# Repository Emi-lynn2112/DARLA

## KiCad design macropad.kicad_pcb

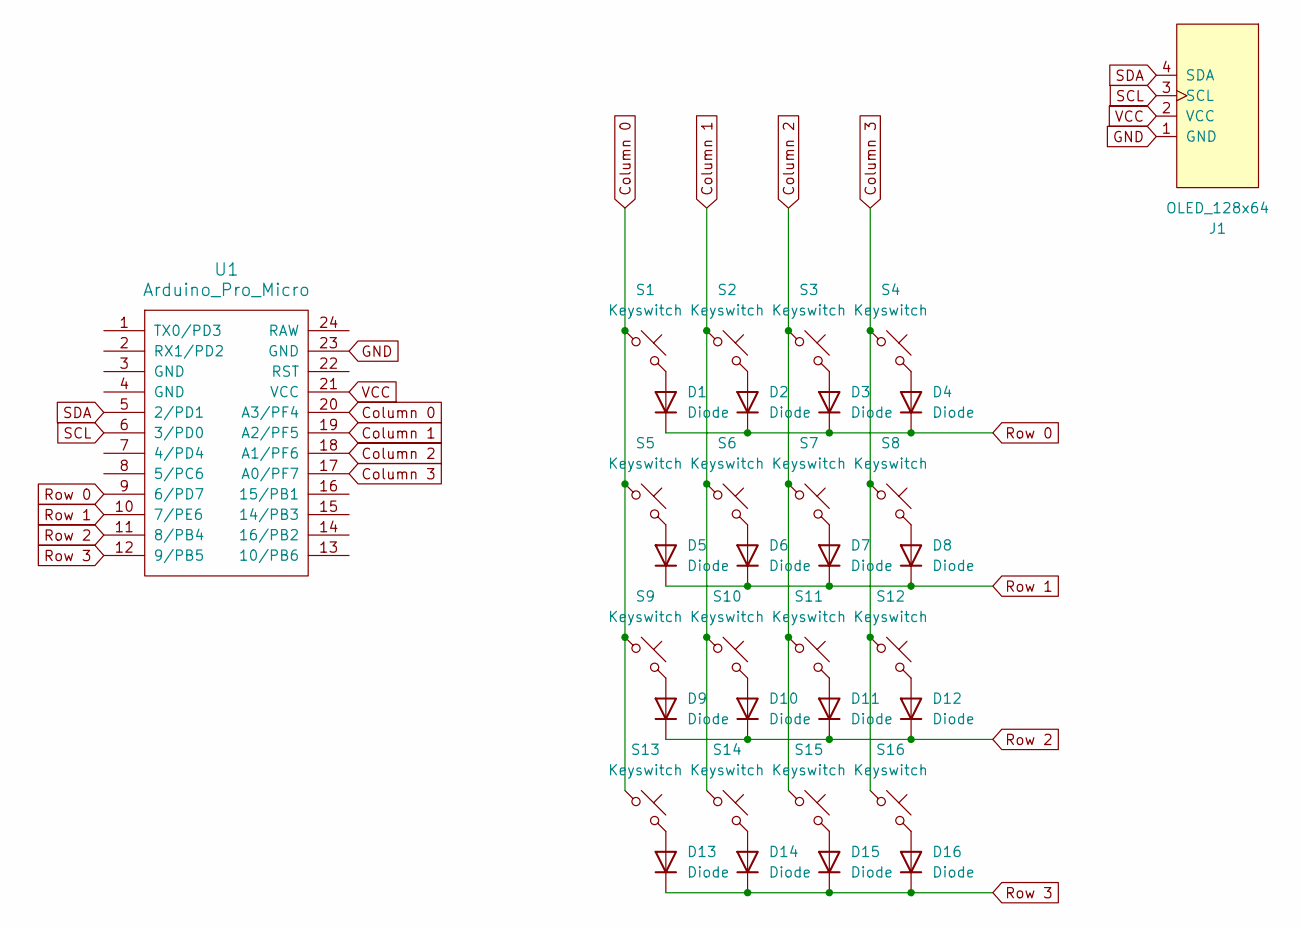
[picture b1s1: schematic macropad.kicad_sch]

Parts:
D1, D2, D3, D4, D5, D6, D7, D8, D9, D10, D11, D12, D13, D14, D15, D16: Diode; Diode_SOD-123
J1: OLED_128x64
S1, S2, S3, S4, S5, S6, S7, S8, S9, S10, S11, S12, S13, S14, S15, S16: Keyswitch; MX_PCB_1.00u
U1: Arduino_Pro_Micro

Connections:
Column 0: S1.1, S5.1, S9.1, S13.1, U1.20 (A3/PF4)
Column 1: S2.1, S6.1, S10.1, S14.1, U1.19 (A2/PF5)
Column 2: S3.1, S7.1, S11.1, S15.1, U1.18 (A1/PF6)
Column 3: S4.1, S8.1, S12.1, S16.1, U1.17 (A0/PF7)
GND: J1.1 (GND), U1.23 (GND)
unnamed: D1.2 (A), S1.2
unnamed: D2.2 (A), S2.2
unnamed: D3.2 (A), S3.2
unnamed: D4.2 (A), S4.2
unnamed: D5.2 (A), S5.2
unnamed: D6.2 (A), S6.2
unnamed: D7.2 (A), S7.2
unnamed: D8.2 (A), S8.2
unnamed: D9.2 (A), S9.2
unnamed: D10.2 (A), S10.2
unnamed: D11.2 (A), S11.2
unnamed: D12.2 (A), S12.2
unnamed: D13.2 (A), S13.2
unnamed: D14.2 (A), S14.2
unnamed: D15.2 (A), S15.2
unnamed: D16.2 (A), S16.2
Row 0: D1.1 (K), D2.1 (K), D3.1 (K), D4.1 (K), U1.9 (6/PD7)
Row 1: D5.1 (K), D6.1 (K), D7.1 (K), D8.1 (K), U1.10 (7/PE6)
Row 2: D9.1 (K), D10.1 (K), D11.1 (K), D12.1 (K), U1.11 (8/PB4)
Row 3: D13.1 (K), D14.1 (K), D15.1 (K), D16.1 (K), U1.12 (9/PB5)
SCL: J1.3 (SCL), U1.6 (3/PD0)
SDA: J1.4 (SDA), U1.5 (2/PD1)
VCC: J1.2 (VCC), U1.21 (VCC)

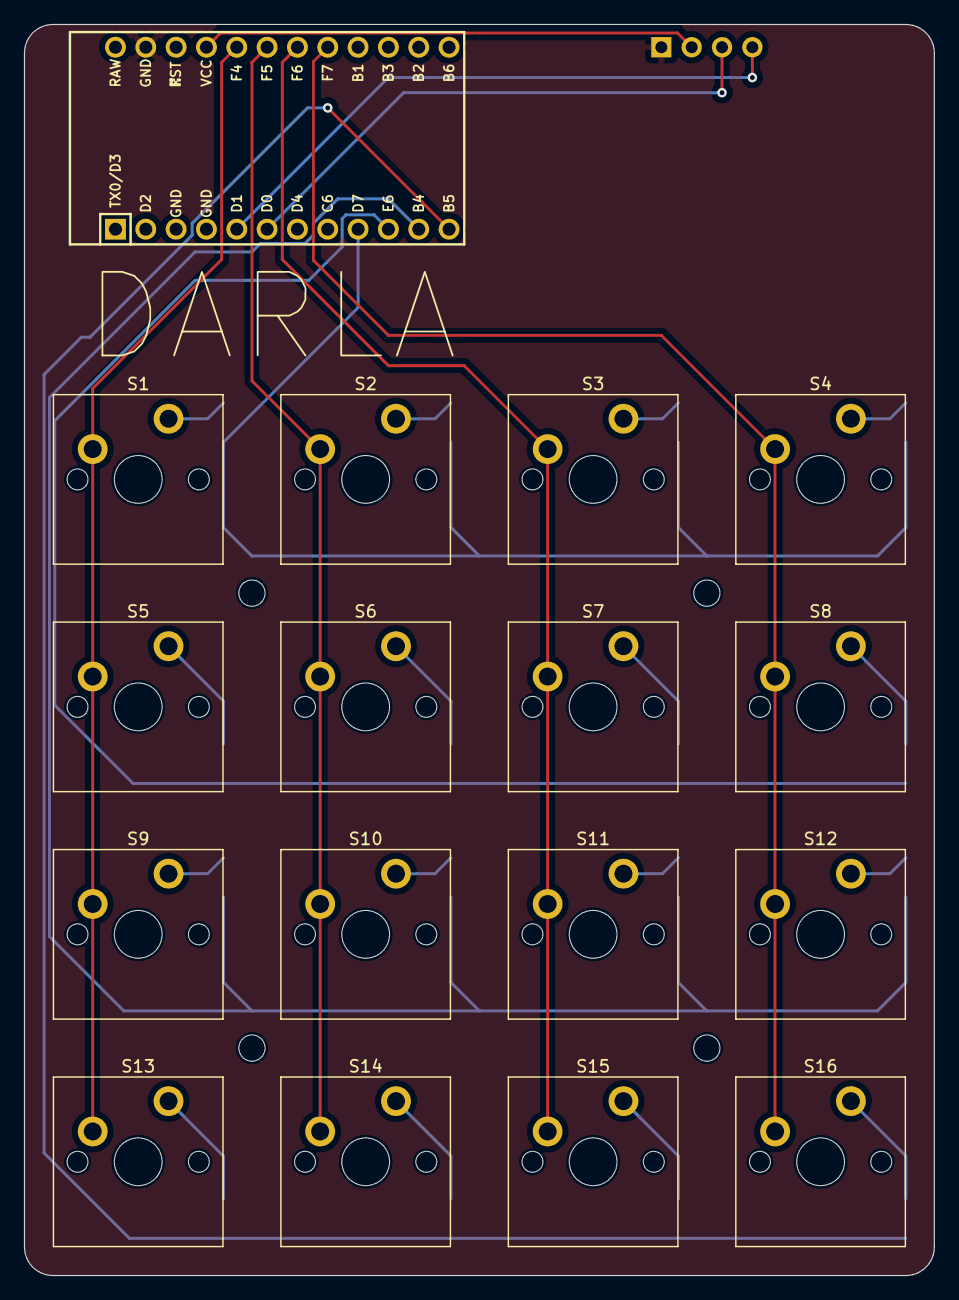
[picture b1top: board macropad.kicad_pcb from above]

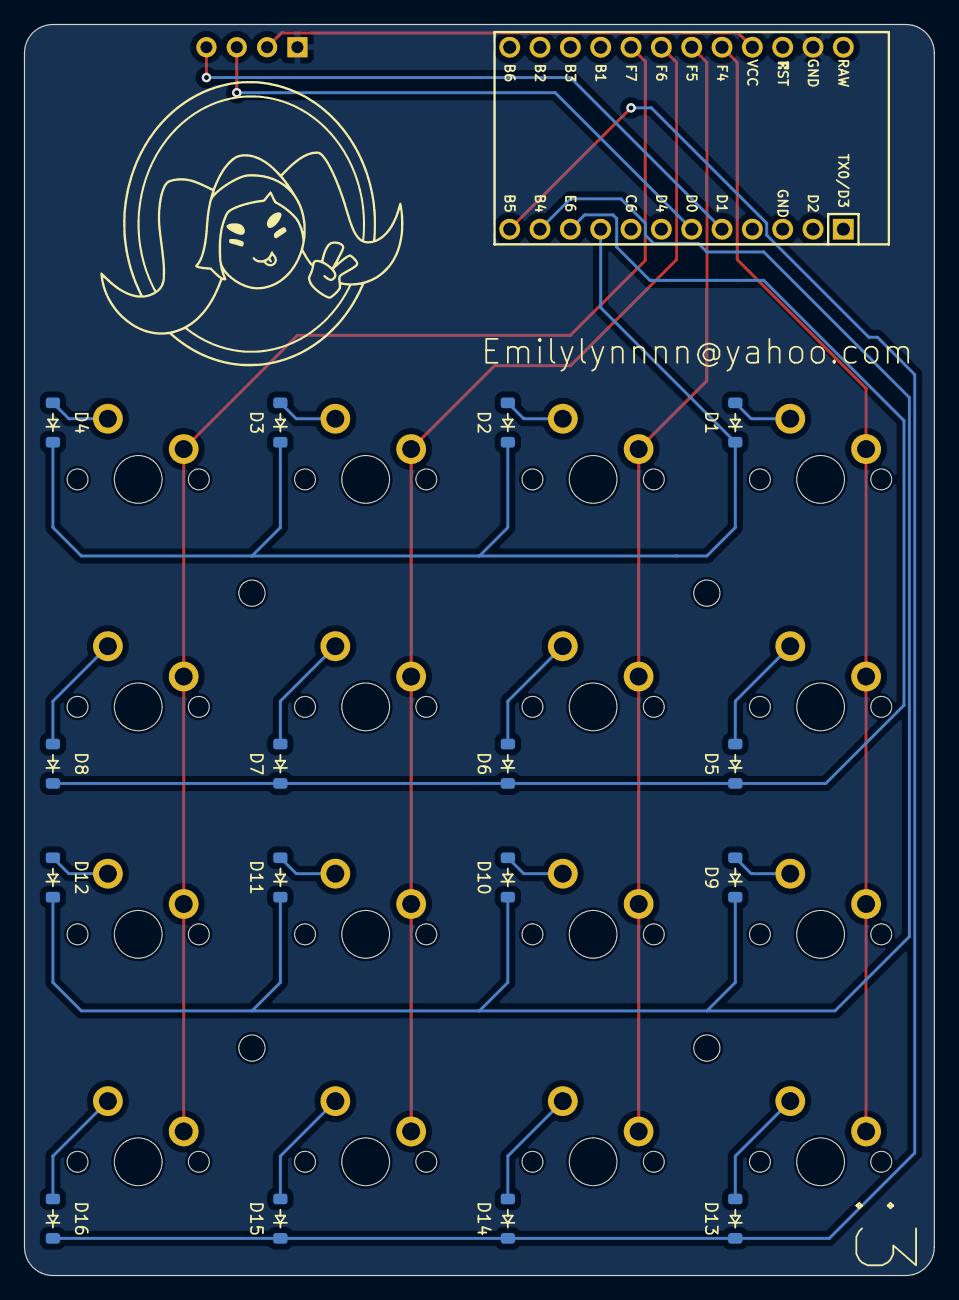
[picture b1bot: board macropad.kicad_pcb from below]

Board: 2 copper layers, 76.2 x 104.8 mm, 34 parts (16 on the bottom side), 28 nets.

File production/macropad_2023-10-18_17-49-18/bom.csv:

Designator,Footprint,Quantity,Value,LCSC Part #
"D1, D10, D11, D12, D13, D14, D15, D16, D2, D3, D4, D5, D6, D7, D8, D9",Diode_SOD-123,16,Diode,
J1,OLED_128x64,1,OLED_128x64,
"S1, S10, S11, S12, S13, S14, S15, S16, S2, S3, S4, S5, S6, S7, S8, S9",MX_PCB_1.00u,16,Keyswitch,
U1,Arduino_Pro_Micro,1,Arduino_Pro_Micro,
